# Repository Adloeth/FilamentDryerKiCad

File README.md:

# FilamentDryer KiCad

This is my first ever PCB design, nothing too interesting.

As this is my first electronic project with a custom PCB, this whole thing is a mess and I wouldn't do anything like this ever again ^^'

A lot of lessons were learned. I ordered and tested the board and everything is working as expected, but because I was ignorant there is a chance the whole PCB is a ticking bomb especially considering I totally forgot everything about it. Younger me might have miscalculated (or simply not calculated at all) some power usage somewhere, and it is possible a resistor, trace, component or whatever burst in flames and magic smokes.

## The Board

There aren't really that many components on this board, except a few resistors and MOSFETs. It mostly is a scaffolding for other PCBs : 
* Arduino Nano
* TCA9548A I²C multiplexer
* LM2596 buck converter to lower the voltage to 5V for the Arduino

The board has other peripherals :
* The DC 12V 5W 80°C PTC heating element
* AT24C256, an I²C EEPROM to store the temperature and humidity graphs.
* DHT22 sensor to control the heating element
* Two I²C OLED screens
* PC fan
* Loadcell and the HX711 (it's amplifier) to measure how many filament is left
* A few buttons to control everything

The Arduino code can be found on [another repository](https://github.com/Adloeth/FilamentDryer).

## Why I did all this

My 3D printer had a moisture problem (Apparently PETG doesn't like humidity that much). The solution to this problem was to put the filament in the oven for a few hours, but I am not dumb enough to put a plastic that can have any number of toxic additives in the same oven I used to bake the food I eat.

Some companies sell filament dryers, the lowest of which was 60€ at the time. After looking around on the Internet I found a [series of videos](https://www.youtube.com/watch?v=IPKQCZ75Vwg&list=PLU5lZZLWyxXBlUrfcWFHtYylawElMm2N6) from [My Tech Fun](https://www.youtube.com/@MyTechFun) comparing several dryers, the ones at the lowest prices were surprisingly ineffective and required a lot of DIY to make them more efficient. While the most expansive were absolutely overkill.

So I decided to make everything myself, making sure my dryer was working where the other ones wouldn't and that some features only the priciest had were available to mine. The whole BOM was to be around 70€, which was good enough. It even had extruded polystyrene for thermal insulation !

Ultimately, putting my filament in an IKEA 10.6L 365+ with a layer of silica gel at the bottom solved the moisture issue and this project only served for me to learn how to make and order PCBs using KiCad and [JLCPCB](https://jlcpcb.com/), which is a very useful skill for my other future projects. Maybe one day I'll properly finish it, especially if I ever buy polyamide filaments.

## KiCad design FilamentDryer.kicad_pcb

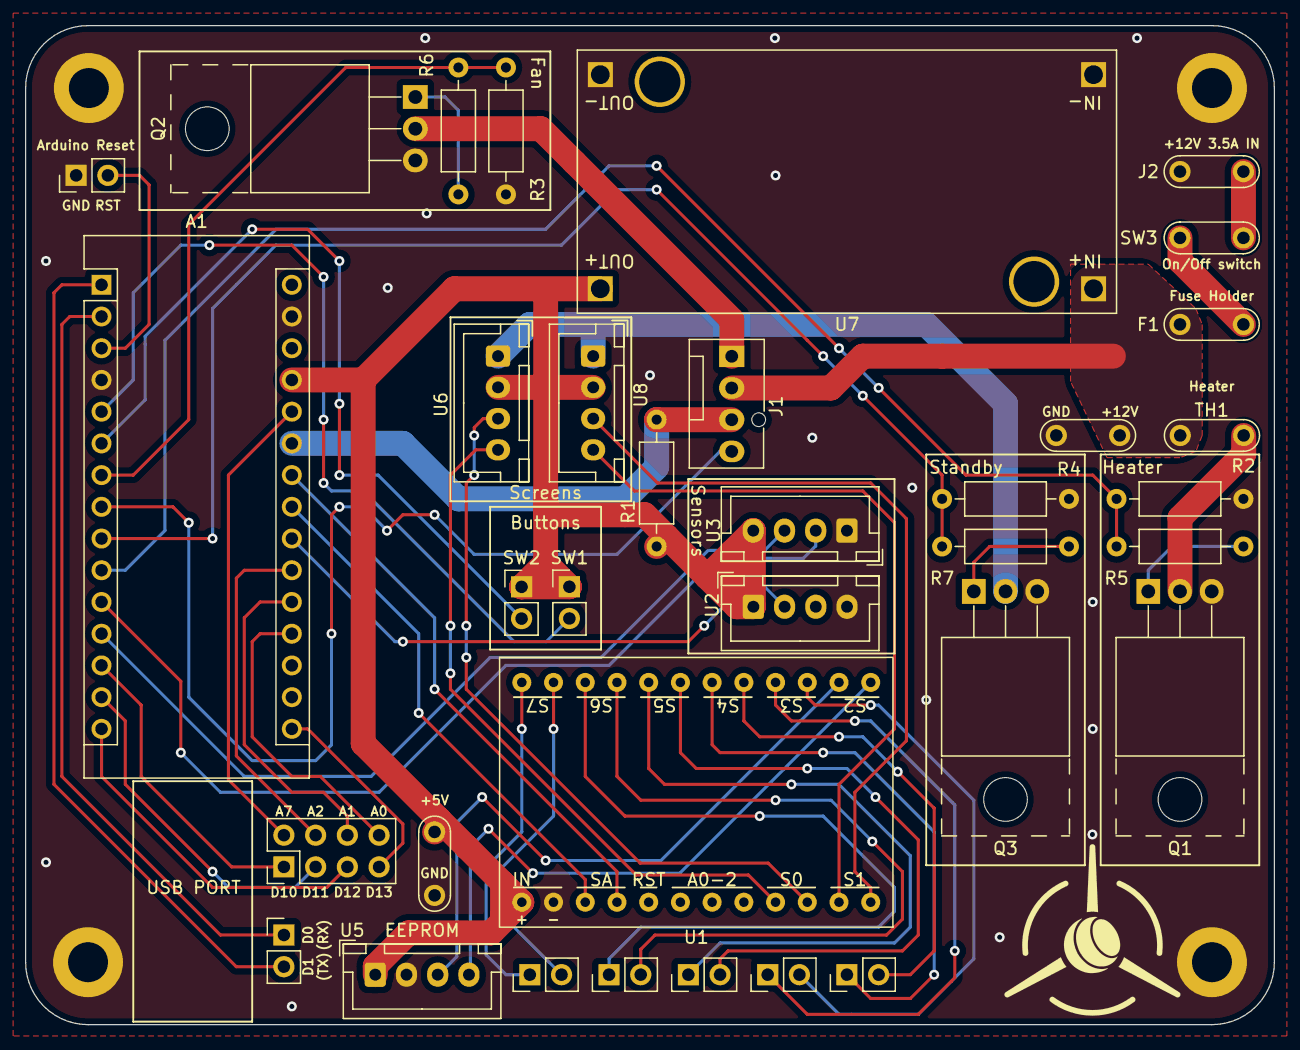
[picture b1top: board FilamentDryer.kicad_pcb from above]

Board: 2 copper layers, 100.0 x 80.0 mm, 27 parts (0 on the bottom side), 29 nets.

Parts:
+5V_GND, +5V_GND#2: 7A_Connector_2Pin
A1: Arduino_Nano_v3.x; Arduino_Nano
F1: Fuse; 7A_Connector_2Pin
J1: Conn_01x04; FanPinHeader_1x04_P2.54mm_Vertical
J2: Barrel_Jack_Switch; 7A_Connector_2Pin
Q1, Q2, Q3: IRF540N; TO-220-3_Horizontal_TabUp
R1: 330; R_Axial_DIN0207_L6.3mm_D2.5mm_P10.16mm_Horizontal
R2, R3, R4: 10k; R_Axial_DIN0207_L6.3mm_D2.5mm_P10.16mm_Horizontal
R5, R6, R7: 220; R_Axial_DIN0207_L6.3mm_D2.5mm_P10.16mm_Horizontal
SW1, SW2: SW_Push; PinHeader_1x02_P2.54mm_Vertical
SW3: SW_SPST; 7A_Connector_2Pin
TH1: Thermistor_PTC; 7A_Connector_2Pin
U1: TCA9548A
U2: DHT22; JST_XH_B4B-XH-A_1x04_P2.50mm_Vertical
U3: HX711; JST_XH_B4B-XH-A_1x04_P2.50mm_Vertical
U5: AT24CXX; JST_XH_B4B-XH-A_1x04_P2.50mm_Vertical
U6, U8: OLED; JST_XH_B4B-XH-A_1x04_P2.50mm_Vertical
U7: LM2596S-ADJ-PCB; LM2596

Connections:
/ControlCircuit/+5V: +5V_GND#2.2, A1.27 (+5V), R1.1, SW1.1, SW2.1, U1.1 (VCC), U2.1 (VCC), U3.4 (VCC), U5.1 (VCC), U6.2 (VCC), U7.3 (OUT+), U8.2 (VCC)
/ControlCircuit/FanGND: J1.1, Q2.2 (D)
/ControlCircuit/FanPWM: A1.8 (D5), J1.4
/ControlCircuit/FanSwitch: A1.7 (D4), R3.1, R6.1
/ControlCircuit/FanTach: A1.25 (A6), J1.3, R1.2
/ControlCircuit/HeaterGND: Q1.2 (D), TH1.1
/ControlCircuit/HeaterSwitch: A1.10 (D7), R2.1, R5.1
/ControlCircuit/INT0: A1.5 (D2), SW1.2
/ControlCircuit/INT1: A1.6 (D3), SW2.2
/ControlCircuit/LCDAT: A1.11 (D8), U3.2 (DAT)
/ControlCircuit/LCSCK: A1.12 (D9), U3.3 (SCK)
/ControlCircuit/SBSwitch: A1.9 (D6), R4.1, R7.1
/ControlCircuit/SCL: A1.24 (A5), U1.4 (SCL)
/ControlCircuit/SDA: A1.23 (A4), U1.3 (SDA)
/ControlCircuit/U2A: A1.22 (A3), U2.2 (DAT)
/PowerSupply/+12V: +5V_GND.1, F1.2, J1.2, TH1.2, U7.1 (IN+)
GND: +5V_GND.2, +5V_GND#2.1, A1.4 (GND), A1.29 (GND), J2.2, Q1.3 (S), Q2.3 (S), Q3.3 (S), R2.2, R3.2, R4.2, U1.2 (GND), U2.4 (GND), U3.1 (GND), U5.2 (GND), U7.2 (IN-), U7.4 (OUT-)
GNDSB: Q3.2 (D), U6.1 (GND), U8.1 (GND)
unnamed: F1.1, SW3.2 (B)
unnamed: J2.1, SW3.1 (A)
unnamed: Q1.1 (G), R5.2
unnamed: Q2.1 (G), R6.2
unnamed: Q3.1 (G), R7.2
unnamed: U1.9 (SDA0), U6.4 (SDA)
unnamed: U1.10 (SCL0), U6.3 (SCL)
unnamed: U1.11 (SDA1), U8.4 (SDA)
unnamed: U1.12 (SCL1), U8.3 (SCL)
unnamed: U1.13 (SDA2), U5.4 (SDA)
unnamed: U1.14 (SCL2), U5.3 (SCL)

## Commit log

2023-04-23 added gitignore
2023-04-23 docs: updated README.md
2023-04-23 removed schematic
2023-04-23 removed cache
